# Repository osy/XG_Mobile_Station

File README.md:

XG Mobile Dock
==============
This open source hardware allows you to connect any PCIe card to an ASUS ROG device with the XG Mobile connector.

The standard variant is a drop-in replacement PCB for the [XG Station Pro Thunderbolt 3 eGPU dock][1]. It contains a built in USB 3.1 Gen 2 hub and a USB PD charger.

The lite variant is a standalone board that is compatible in dimensions with the [ADT-UT3G][6]. It requires a standard ATX power supply and passes through the USB to an external port.

## Features
* Up to PCIe 4.0 x8 support for 2021/2022/2023 ROG Flow
* Up to PCIe 4.0 x4 support for 2023 ROG Ally
* MCU handling cable detection and LEDs
* 65W USB PD charger (standard variant)
* 2 USB-C ports connected to a USB 3.1 Gen 2 hub (standard variant)
* 300W DC-DC power supply (standard variant)

## Getting Started
1. [Build the PCB](Docs/Build_Guide.md)
2. [Flash the board](#flashing-firmware)
3. [Install the software](#install-xgmactivator)

### Flashing Firmware
Lite boards only need to flash STM32 while the standard board requires writing two SPI flash as well.

#### STM32 MCU
1. Download `XG_Mobile_Dock_MCU.bin` from the latest release or [build your own](Docs/Build_Guide.md#mcu).
2. Download and install [ST32CubeProgrammer][2].
3. Connect your ST-LINK v2 to your computer. Note if you are using a cheap clone from Amazon or Aliexpress, the pin numbers printed on the device may be incorrect.
4. Connect the SWDIO, SWCLK, and GND pins to J10 on the board to the ST-LINK v2. Do not connect +3V3. If you are using an official ST-LINK, you will need a jumper wire from VAPP (pin 1) to VDD (pin 19).
5. Ensure the board is powered on so it can be programmed.
6. Open ST32CubeProgrammer and go to the "Erasing & programming" page (second icon on the left sidebar).
7. Browse and select the firmware file.
8. Check "Run after programming"
9. Click "Connect" on the right sidebar and then "Start Programming" on the left.

#### SPI Flash for TI USB PD
We will be using a Raspberry Pi, although most other SBC can also work as well as dedicated SPI flashers.

1. [Enable the SPI interface on the Raspberry Pi.][3]
2. Connect GND (Ground), SS (SPI0 CE0), CLK (SPI0 SCLK), MISO (SPI0 MISO), and MOSI (SPI0 MOSI) on J9 [to the Raspberry Pi][4].
3. Open a shell to the Raspberry Pi and install Flashrom: `sudo apt-get install flashrom`
4. Download `XG_Mobile_Dock_Charger.bin` from the latest release or [build your own](Docs/Build_Guide.md#ti-pd-controller).
5. Flash the firmware: `sudo flashrom -p linux_spi:dev=/dev/spidev0.0,spispeed=1000 -w XG_Mobile_Dock_Charger.bin`

#### SPI Flash for VIA USB Hub
We will be using a Raspberry Pi, although most other SBC can also work as well as dedicated SPI flashers.

1. [Enable the SPI interface on the Raspberry Pi.][3]
2. Connect GND (Ground), SS (SPI0 CE0), CLK (SPI0 SCLK), MISO (SPI0 MISO), and MOSI (SPI0 MOSI) on J13 [to the Raspberry Pi][4]. Note the order of the pins is different from J9.
3. Open a shell to the Raspberry Pi and install Flashrom if it is not already installed: `sudo apt-get install flashrom`
4. Download `VL822_Q7_9043_Phantom_20220616.bin` from the latest release.
5. Flash the firmware: `sudo flashrom -p linux_spi:dev=/dev/spidev0.0,spispeed=1000 -w VL822_Q7_9043_Phantom_20220616.bin`

### Install XGMDriver
XGMDriver tricks ARMORY CRATE software into identifying the custom dock as an official XG Mobile device. Once installed, it should work even if ARMORY CRATE software is updated. You can check out the [source code here](XGMDriver).

1. Download `XGMDriverSetup.exe` from the latest release.
2. Run the installer making sure to correctly select AMD or NVIDIA depending on the vendor of the GPU you are installing.
3. If you need to swap between AMD and NVIDIA, uninstall from Control Panel or by running the installer again. Then you can re-install and select the right option.

## Troubleshooting

### Error 43 or no video output on NVIDIA GPUs
This is a well known issue with NVIDIA eGPUs. Once the eGPU is installed along with the correct drivers, you will need to install [this script][5].

### PCIe is only getting 3.0 speeds after hot plugging
You need to restart your device. For some reason, hot plugging results in 3.0 speeds.

### Unable to get 4.0 speeds
If you observe any of the following:
* GPU-Z changes between 4.0 and lower versions *when under load*
* You observe a lot of stuttering or < 10 FPS in 1% lows
* Windows behaves extremely slowly (moving the mouse cursor will take > 1 sec to respond)
* Event viewer for System shows multiple times: "WHEA-Logger Event ID:17 - A corrected hardware error has occurred"

Then the device is having trouble sustaining PCIe 4.0 speeds. This can be caused by any combination of the following issues:

1. The board was not manufactured properly with impedance matching or the high speed connectors were not properly soldered. Verify that the boards were manufactured with the correct specifications and test multiple boards.
2. The GPU is malfunctioning or is not mounted correctly. Make sure you can obtain PCIe 4.0 speeds on a desktop PC.
3. The XGM cable is not connected to the board correctly. Make sure the two 40P connectors are tight and the metal bar is locked over the connector to prevent unintentional loosening. Make sure the shielding screw is tightly screwed to the screw terminal next to the connector. Make sure the cable isn't twisted or bent any more than it needs to be. If the XGM cable came coiled up, try to carefully straighten it.
4. The XGM cable is not manufactured correctly. The official XGM device only supports PCIe 3.0 speeds so the cable is only rated for PCIe 3.0. We found that some cables are easier to get 4.0 speeds working than other cables so there is some manufacturing variance.

You can run FurMark for a long duration and observe the GPU load to check that it is able to maintain 4.0 speeds. If the GPU is constantly trying to switch speeds, you will observe large FPS drops and large dips in the GPU usage percentage. You can also use CUDA-Z to check the access speeds while under load.

If you cannot maintain PCIe 4.0 speeds, you can always do a hot-unplug and hot-plug to force it to run in PCIe 3.0 mode.

### No popup when XGM is connected
Sometimes, the device will not be detected and you can flip the lock switch off and on again to force the software to re-detect the device.

### "It appears that your XG Mobile is not properly connected..."
If you get a pop-up saying XG Mobile is not properly connected, make sure [XGMDriver](#install-xgmdriver) is installed. If this is still an issue with XGMDriver installed, there is likely a connection issue with the cable.

### ASUS Driver install popup on reboot
Re-install XGMDriver to inhibit the ASUS driver popup.

### Lite: USB is not detected
The lite board does not have USB orientation detection. Try flipping the USB-C cable upside down and try again.

## References
Knowledge base for all things XGM gathered from reverse engineering the hardware and software.

* [XGM connector information](Docs/Connector.md)
* [XGM software interfaces](Docs/Software.md)
* [MCU command interface](Docs/MCU.md)
* [PCB design diary](Docs/Diary.md)
* [Reversed ACPI tables](Docs/ACPI_Annotated.asl)
* [Reversed BIOS detection](Docs/BIOS_Detect.c)

## Related Projects

* [Modified Lite design with redrivers for improved performance (not yet working)](https://github.com/Alecu100/XG_Mobile_Station/tree/flow_v2)

[1]: https://www.asus.com/motherboards-components/external-graphics-docks/all-series/xg-station-pro/
[2]: https://www.st.com/en/development-tools/stm32cubeprog.html
[3]: https://www.raspberrypi-spy.co.uk/2014/08/enabling-the-spi-interface-on-the-raspberry-pi/
[4]: https://pinout.xyz
[5]: https://egpu.io/nvidia-error43-fixer
[6]: https://www.adt.link/product/UT3G.html

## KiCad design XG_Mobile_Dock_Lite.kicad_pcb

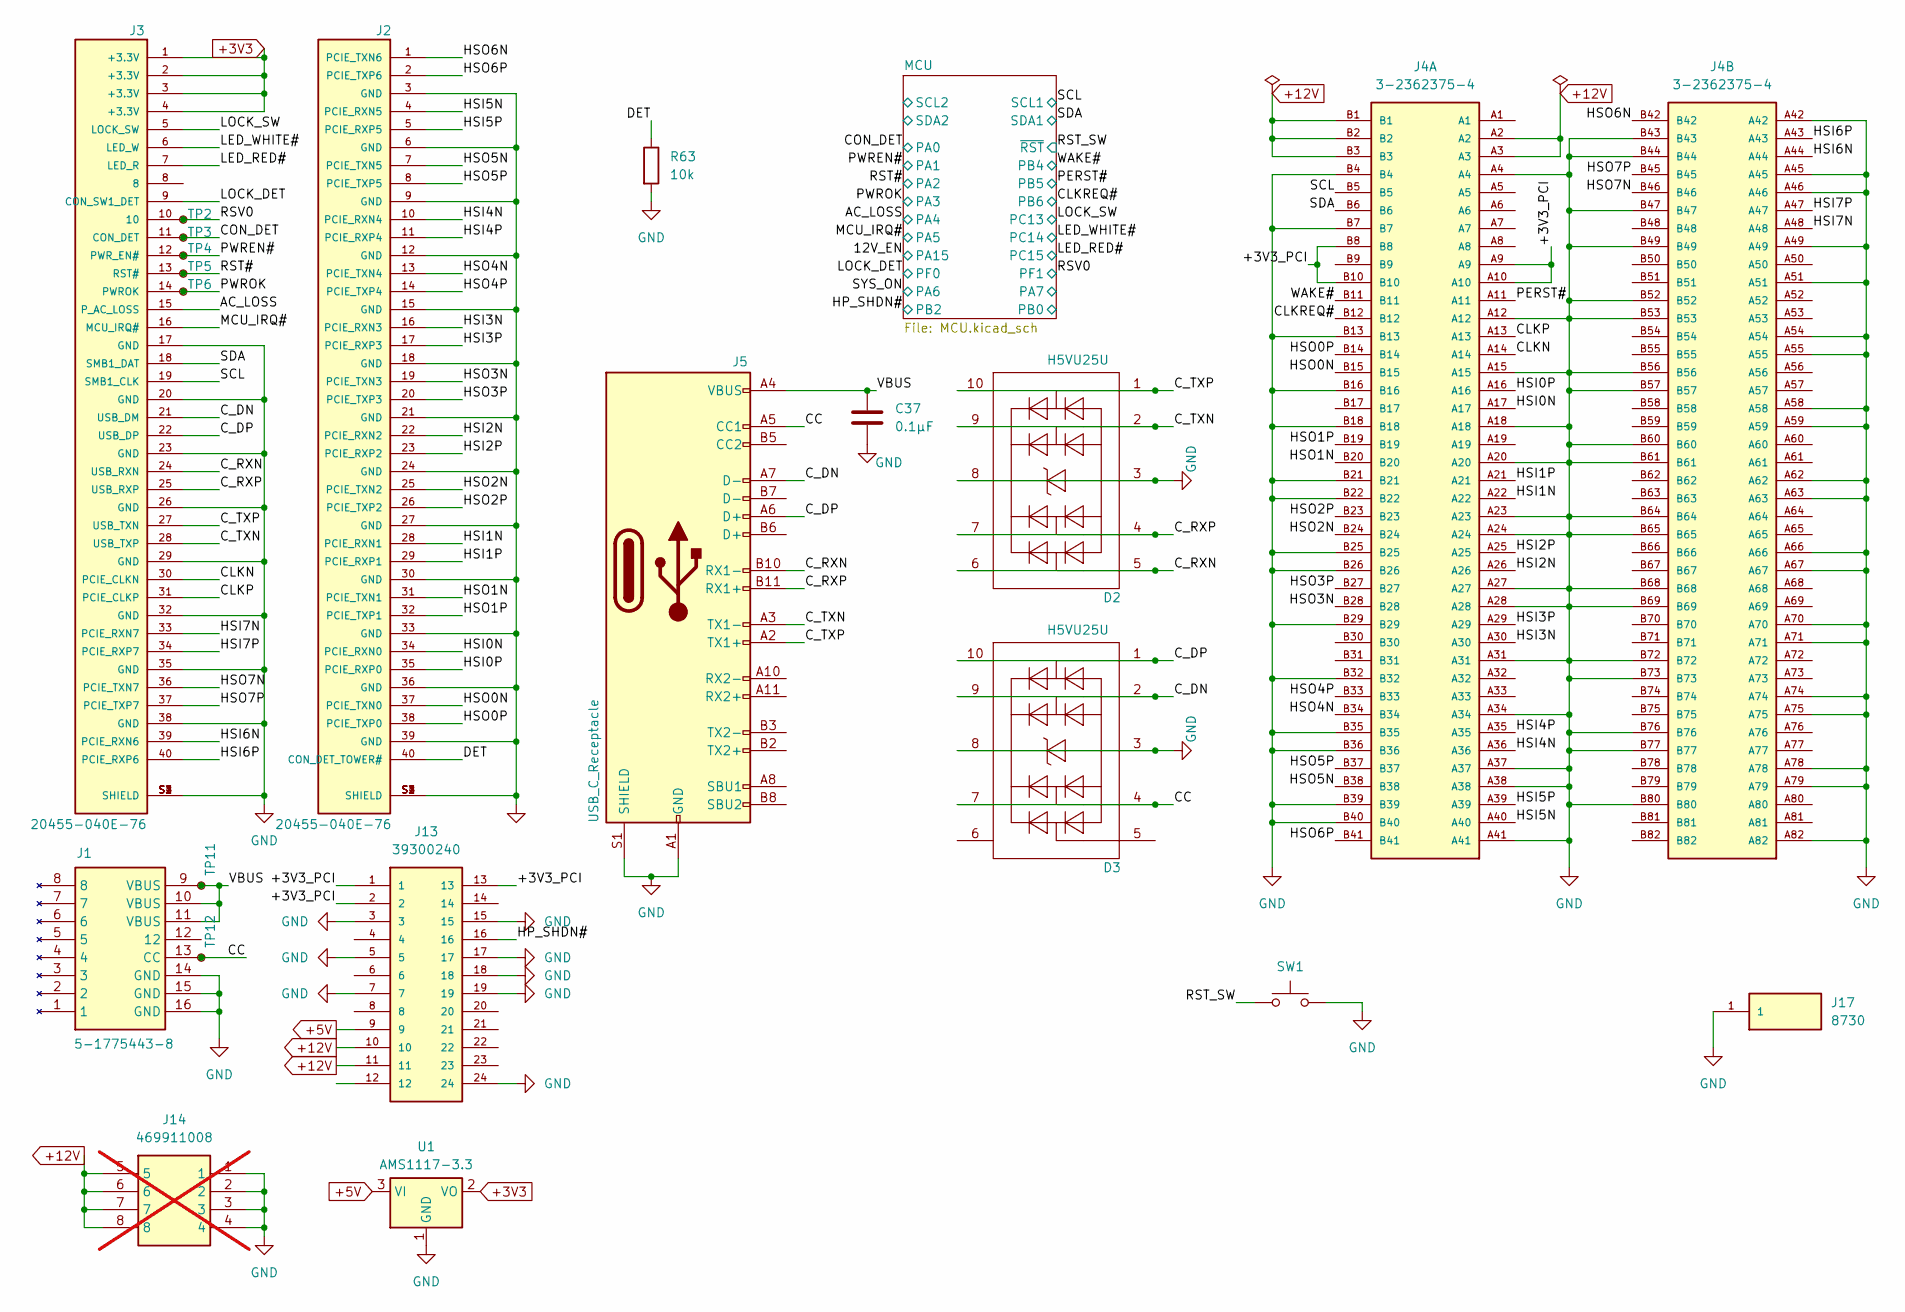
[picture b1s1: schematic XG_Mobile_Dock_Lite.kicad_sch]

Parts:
C37: 0.1μF; C_0402_1005Metric; Part_Number CL05B104KO5NNNC; LCSC C1525
D2, D3: H5VU25U; AZ1045-04F; Part_Number H5VU25U; LCSC C7420374
J1: 5-1775443-8; Manufacturer_Part_Number 5-1775443-8
J2, J3: 20455-040E-76; Part_Number 20455-040E-76; LCSC C5160883
J4: 3-2362375-4; CONN-SMD_164P-P1.00-V_3133; Part_Number 3113-113T; LCSC C404104
J5: USB_C_Receptacle; USB-C-SMD_TYPE-C-24P-QT; Part_Number TYPE-C 24P QT; LCSC C2681555
J13: 39300240; CON_39300240; Part_Number ZX-5557-4.2-2-12PWZ; LCSC C7541574
J14: 469911008; CON_469911008; Part_Number 469911008; LCSC C17470577; not fitted
J17: 8730; KEYSTONE_8730; PARTREV C
R63: 10k; R_0402_1005Metric; Part_Number 0402WGF1002TCE; LCSC C25744
SW1: SW_Push; SW_SPST_SKQG_WithStem; Part_Number TS-1187A-B-A-B; LCSC C318884
TP2, TP3, TP4, TP5, TP6, TP11, TP12: TestPoint_Small; TestPoint_Pad_D1.0mm
U1: AMS1117-3.3; SOT-223-3_TabPin2; Part_Number AMS1117-3.3; LCSC C6186

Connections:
+3V3: J3.1 (+3.3V), J3.2 (+3.3V), J3.3 (+3.3V), J3.4 (+3.3V), U1.2 (VO); also elsewhere on the board
+5V: J13.9, U1.3 (VI); also elsewhere on the board
+12V: J4.A2, J4.A3, J4.B1, J4.B2, J4.B3, J13.10, J13.11, J14.5, J14.6, J14.7, J14.8; also elsewhere on the board
/+3V3_PCI: J4.A9, J4.A10, J4.B8, J4.B10, J13.1, J13.2, J13.13
/AC_LOSS: J3.15 (P_AC_LOSS); also elsewhere on the board
/CC: D3.4 (I/O_3), D3.7 (NC), J1.13 (CC), J5.A5 (CC1), TP12.1
/CLKN: J3.30 (PCIE_CLKN), J4.A14
/CLKP: J3.31 (PCIE_CLKP), J4.A13
/CLKREQ#: J4.B12; also elsewhere on the board
/CON_DET: J3.11 (CON_DET), TP3.1; also elsewhere on the board
/C_DN: D3.2 (I/O_2), D3.9 (NC), J3.21 (USB_DM), J5.A7 (D-)
/C_DP: D3.1 (I/O_1), D3.10 (NC), J3.22 (USB_DP), J5.A6 (D+)
/C_RXN: D2.5 (I/O_4), D2.6 (NC), J3.24 (USB_RXN), J5.B10 (RX1-)
/C_RXP: D2.4 (I/O_3), D2.7 (NC), J3.25 (USB_RXP), J5.B11 (RX1+)
/C_TXN: D2.2 (I/O_2), D2.9 (NC), J3.28 (USB_TXP), J5.A3 (TX1-)
/C_TXP: D2.1 (I/O_1), D2.10 (NC), J3.27 (USB_TXN), J5.A2 (TX1+)
/DET: J2.40 (CON_DET_TOWER#), R63.1
/HP_SHDN#: J13.16; also elsewhere on the board
/HSI0N: J2.34 (PCIE_RXN0), J4.A17
/HSI0P: J2.35 (PCIE_RXP0), J4.A16
/HSI1N: J2.28 (PCIE_RXN1), J4.A22
/HSI1P: J2.29 (PCIE_RXP1), J4.A21
/HSI2N: J2.22 (PCIE_RXN2), J4.A26
/HSI2P: J2.23 (PCIE_RXP2), J4.A25
/HSI3N: J2.16 (PCIE_RXN3), J4.A30
/HSI3P: J2.17 (PCIE_RXP3), J4.A29
/HSI4N: J2.10 (PCIE_RXN4), J4.A36
/HSI4P: J2.11 (PCIE_RXP4), J4.A35
/HSI5N: J2.4 (PCIE_RXN5), J4.A40
/HSI5P: J2.5 (PCIE_RXP5), J4.A39
/HSI6N: J3.39 (PCIE_RXN6), J4.A44
/HSI6P: J3.40 (PCIE_RXP6), J4.A43
/HSI7N: J3.33 (PCIE_RXN7), J4.A48
/HSI7P: J3.34 (PCIE_RXP7), J4.A47
/HSO0N: J2.37 (PCIE_TXN0), J4.B15
/HSO0P: J2.38 (PCIE_TXP0), J4.B14
/HSO1N: J2.31 (PCIE_TXN1), J4.B20
/HSO1P: J2.32 (PCIE_TXP1), J4.B19
/HSO2N: J2.25 (PCIE_TXN2), J4.B24
/HSO2P: J2.26 (PCIE_TXP2), J4.B23
/HSO3N: J2.19 (PCIE_TXN3), J4.B28
/HSO3P: J2.20 (PCIE_TXP3), J4.B27
/HSO4N: J2.13 (PCIE_TXN4), J4.B34
/HSO4P: J2.14 (PCIE_TXP4), J4.B33
/HSO5N: J2.7 (PCIE_TXN5), J4.B38
/HSO5P: J2.8 (PCIE_TXP5), J4.B37
/HSO6N: J2.1 (PCIE_TXN6), J4.B42
/HSO6P: J2.2 (PCIE_TXP6), J4.B41
/HSO7N: J3.36 (PCIE_TXN7), J4.B46
/HSO7P: J3.37 (PCIE_TXP7), J4.B45
/LED_RED#: J3.7 (LED_R); also elsewhere on the board
/LED_WHITE#: J3.6 (LED_W); also elsewhere on the board
/LOCK_DET: J3.9 (CON_SW1_DET); also elsewhere on the board
/LOCK_SW: J3.5 (LOCK_SW); also elsewhere on the board
/MCU_IRQ#: J3.16 (MCU_IRQ#); also elsewhere on the board
/PERST#: J4.A11; also elsewhere on the board
/PWREN#: J3.12 (PWR_EN#), TP4.1; also elsewhere on the board
/PWROK: J3.14 (PWROK), TP6.1; also elsewhere on the board
/RST#: J3.13 (RST#), TP5.1; also elsewhere on the board
/RST_SW: SW1.1; also elsewhere on the board
/RSV0: J3.10, TP2.1; also elsewhere on the board
/SCL: J3.19 (SMB1_CLK), J4.B5; also elsewhere on the board
/SDA: J3.18 (SMB1_DAT), J4.B6; also elsewhere on the board
/VBUS: C37.1, J1.9 (VBUS), J1.10 (VBUS), J1.11 (VBUS), J5.A4 (VBUS), J5.A9 (VBUS), J5.B4 (VBUS), J5.B9 (VBUS), TP11.1
/WAKE#: J4.B11; also elsewhere on the board
GND: C37.2, D2.3 (GND), D2.8 (GND), D3.3 (GND), D3.8 (GND), J1.14 (GND), J1.15 (GND), J1.16 (GND), J2.3 (GND), J2.6 (GND), J2.9 (GND), J2.12 (GND), J2.15 (GND), J2.18 (GND), J2.21 (GND), J2.24 (GND), J2.27 (GND), J2.30 (GND), J2.33 (GND), J2.36 (GND), J2.39 (GND), J2.S1 (SHIELD), J2.S2 (SHIELD), J2.S3 (SHIELD), J2.S4 (SHIELD), J3.17 (GND), J3.20 (GND), J3.23 (GND), J3.26 (GND), J3.29 (GND), J3.32 (GND), J3.35 (GND), J3.38 (GND), J3.S1 (SHIELD), J3.S2 (SHIELD), J3.S3 (SHIELD), J3.S4 (SHIELD), J4.A4, J4.A12, J4.A15, J4.A18, J4.A20, J4.A23, J4.A24, J4.A27, J4.A28, J4.A31, J4.A34, J4.A37, J4.A38, J4.A41, J4.A42, J4.A45, J4.A46, J4.A49, J4.A51, J4.A54, J4.A55, J4.A58, J4.A59, J4.A62, J4.A63, J4.A66, J4.A67, J4.A70, J4.A71, J4.A74, J4.A75, J4.A78, J4.A79, J4.A82, J4.B4, J4.B7, J4.B13, J4.B16, J4.B18, J4.B21, J4.B22, J4.B25, J4.B26, J4.B29, J4.B32, J4.B35, J4.B36, J4.B39, J4.B40, J4.B43, J4.B44, J4.B47, J4.B49, J4.B52, J4.B53, J4.B56, J4.B57, J4.B60, J4.B61, J4.B64, J4.B65, J4.B68, J4.B69, J4.B72, J4.B73, J4.B76, J4.B77, J4.B80, J5.A1 (GND), J5.A12 (GND), J5.B1 (GND), J5.B12 (GND), J5.S1 (SHIELD), J13.3, J13.5, J13.7, J13.15, J13.17, J13.18, J13.19, J13.24, J14.1, J14.2, J14.3, J14.4, J17.1, R63.2, SW1.2, U1.1 (GND); also elsewhere on the board

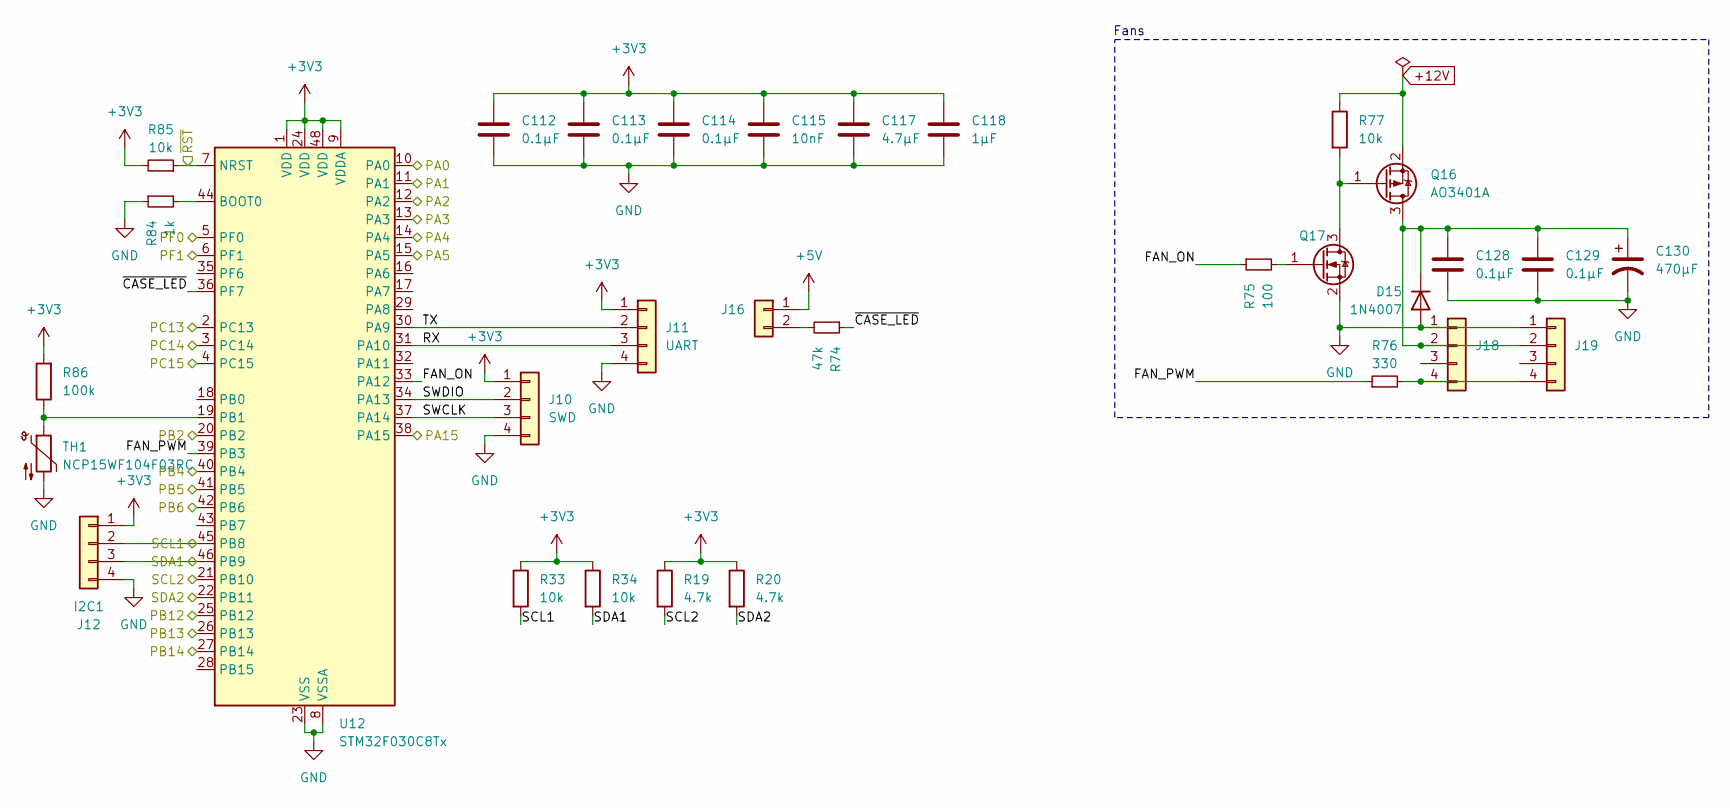
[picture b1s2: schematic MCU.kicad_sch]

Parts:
C112, C113, C114: 0.1µF; C_0402_1005Metric; Part_Number CL05B104KB54PNC; LCSC C307331
C115: 10nF; C_0402_1005Metric; Part_Number CL05B103KB5NNNC; LCSC C15195
C117: 4.7µF; C_0402_1005Metric; Part_Number CL05A475MP5NRNC; LCSC C23733
C118: 1µF; C_0402_1005Metric; Part_Number CL05A105KA5NQNC; LCSC C52923
C128, C129: 0.1µF; C_0603_1608Metric; Part_Number CC0603KRX7R9BB104; LCSC C14663
C130: 470µF; CP_Radial_D10.0mm_P5.00mm; Part_Number EGT477M1HG16RRS0P; LCSC C3015599
D15: 1N4007; D_SOD-123F; Part_Number 1N4007W; LCSC C18199088
J10: SWD; PinHeader_1x04_P2.54mm_Vertical; Part_Number 2.54-1*4; LCSC C5116483
J11: UART; PinHeader_1x04_P2.54mm_Vertical; Part_Number 2.54-1*4; LCSC C5116483
J12: I2C1; PinHeader_1x04_P2.54mm_Vertical; Part_Number 2.54-1*4; LCSC C5116483
J16: JST_PH_S2B-PH-K_1x02_P2.00mm_Horizontal; Part_Number S2B-PH-KL(LF)(SN); LCSC C160237
J18, J19: CONN_SD-47053-001_H10p00_MOL; Part_Number 470531000; LCSC C240840
Q16: AO3401A; SOT-23; Part_Number AO3401A; LCSC C15127
Q17: 2N7002W; SOT-323-3_L2.0-W1.3-P1.30-LS2.1-BR; Part_Number 2N7002W; LCSC C7420322
R19, R20: 4.7k; R_0402_1005Metric; Part_Number 0402WGF4701TCE; LCSC C25900
R33, R34, R77, R85: 10k; R_0402_1005Metric; Part_Number 0402WGF1002TCE; LCSC C25744
R74: 47k; R_0402_1005Metric; Part_Number 0402WGF4702TCE; LCSC C25792
R75: 100; R_0402_1005Metric; Part_Number 0402WGF1000TCE; LCSC C25076
R76: 330; R_0402_1005Metric; Part_Number 0402WGF3300TCE; LCSC C25104
R84: 1k; R_0402_1005Metric; Part_Number 0402WGF1001TCE; LCSC C11702
R86: 100k; R_0402_1005Metric; Part_Number 0402WGF1003TCE; LCSC C25741
TH1: NCP15WF104F03RC; R_0402_1005Metric; Part_Number NCP15WF104F03RC; LCSC C77130
U12: STM32F030C8Tx; LQFP-48_7x7mm_P0.5mm; Part_Number STM32F030C8T6; LCSC C23922

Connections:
+3V3: C112.1, C113.1, C114.1, C115.1, C117.1, C118.1, J10.1, J11.1, J12.1, R19.1, R20.1, R33.1, R34.1, R85.2, R86.2, U12.1 (VDD), U12.9 (VDDA), U12.24 (VDD), U12.48 (VDD); also elsewhere on the board
+5V: J16.1; also elsewhere on the board
+12V: Q16.2 (S), R77.1; also elsewhere on the board
/12V_EN: U12.38 (PA15)
/AC_LOSS: U12.14 (PA4); also elsewhere on the board
/CLKREQ#: U12.42 (PB6); also elsewhere on the board
/CON_DET: U12.10 (PA0); also elsewhere on the board
/HP_SHDN#: U12.20 (PB2); also elsewhere on the board
/LED_RED#: U12.4 (PC15); also elsewhere on the board
/LED_WHITE#: U12.3 (PC14); also elsewhere on the board
/LOCK_DET: U12.5 (PF0); also elsewhere on the board
/LOCK_SW: U12.2 (PC13); also elsewhere on the board
/MCU/FAN_ON: R75.1, U12.33 (PA12)
/MCU/FAN_PWM: R76.1, U12.39 (PB3)
/MCU/PB12: U12.25 (PB12)
/MCU/PB13: U12.26 (PB13)
/MCU/PB14: U12.27 (PB14)
/MCU/RX: J11.3, U12.31 (PA10)
/MCU/SCL2: R19.2, U12.21 (PB10)
/MCU/SDA2: R20.2, U12.22 (PB11)
/MCU/SWCLK: J10.3, U12.37 (PA14)
/MCU/SWDIO: J10.2, U12.34 (PA13)
/MCU/TX: J11.2, U12.30 (PA9)
/MCU/~CASE_LED: R74.1, U12.36 (PF7)
/MCU_IRQ#: U12.15 (PA5); also elsewhere on the board
/PERST#: U12.41 (PB5); also elsewhere on the board
/PWREN#: U12.11 (PA1); also elsewhere on the board
/PWROK: U12.13 (PA3); also elsewhere on the board
/RST#: U12.12 (PA2); also elsewhere on the board
/RST_SW: R85.1, U12.7 (NRST); also elsewhere on the board
/RSV0: U12.6 (PF1); also elsewhere on the board
/SCL: J12.2, R33.2, U12.45 (PB8); also elsewhere on the board
/SDA: J12.3, R34.2, U12.46 (PB9); also elsewhere on the board
/WAKE#: U12.40 (PB4); also elsewhere on the board
GND: C112.2, C113.2, C114.2, C115.2, C117.2, C118.2, C128.2, C129.2, C130.2, D15.2 (A), J10.4, J11.4, J12.4, J18.1, J19.1, Q17.2 (S), R84.1, TH1.2, U12.8 (VSSA), U12.23 (VSS), U12.47 (VSS); also elsewhere on the board
unnamed: C128.1, C129.1, C130.1, D15.1 (K), J18.2, J19.2, Q16.3 (D)
unnamed: J16.2, R74.2
unnamed: J18.4, J19.4, R76.2
unnamed: Q16.1 (G), Q17.3 (D), R77.2
unnamed: Q17.1 (G), R75.2
unnamed: R84.2, U12.44 (BOOT0)
unnamed: R86.1, TH1.1, U12.19 (PB1)

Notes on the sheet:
Fans

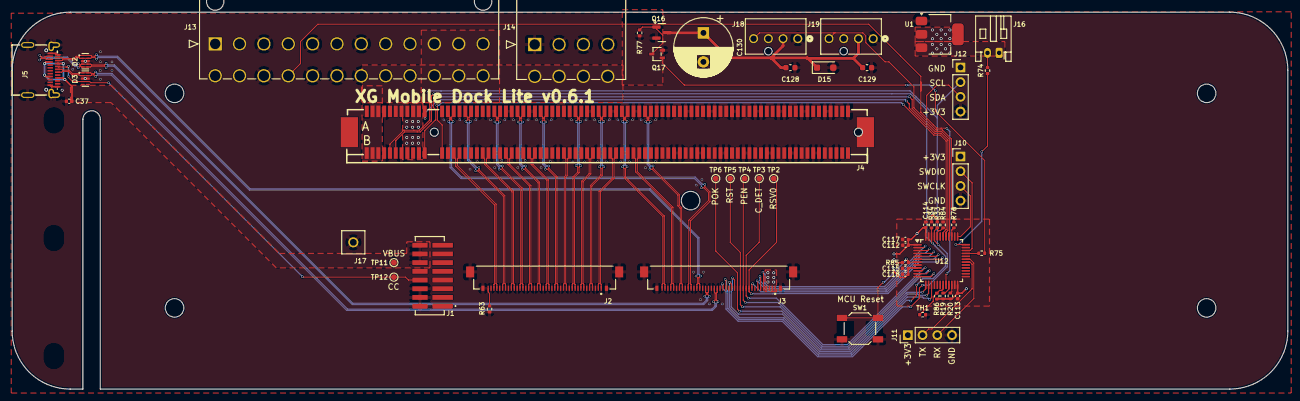
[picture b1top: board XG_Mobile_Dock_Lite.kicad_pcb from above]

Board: 4 copper layers, 220.0 x 65.0 mm, 52 parts (0 on the bottom side), 82 nets.

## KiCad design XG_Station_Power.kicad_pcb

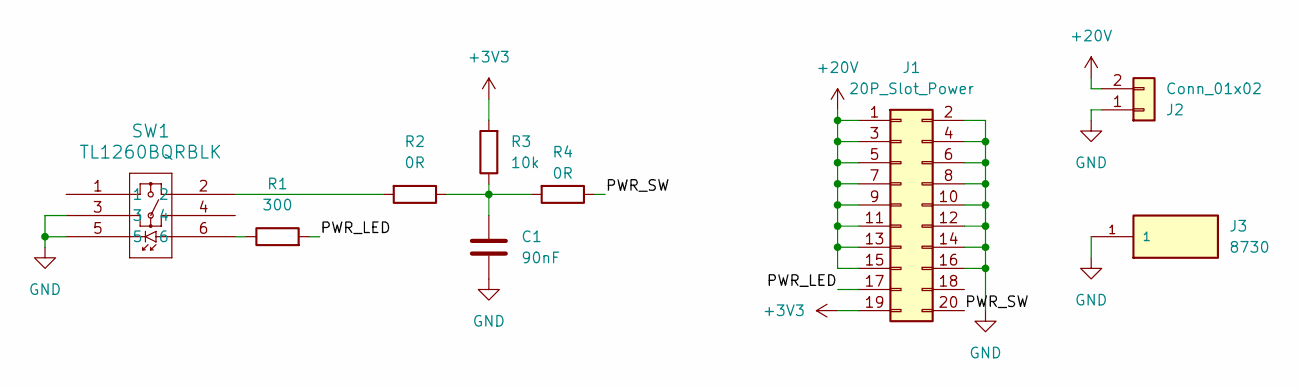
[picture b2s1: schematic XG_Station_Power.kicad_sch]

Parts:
C1: 90nF; C_0402_1005Metric
J1: 20P_Slot_Power
J2: Conn_01x02; 2351970-1
J3: 8730; KEYSTONE_8730; PARTREV C
R1: 300; R_0603_1608Metric
R2, R4: 0R; R_0402_1005Metric
R3: 10k; R_0402_1005Metric
SW1: TL1260BQRBLK; TL1260_EWI

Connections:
+3V3: J1.19, R3.2
+20V: J1.1, J1.3, J1.5, J1.7, J1.9, J1.11, J1.13, J1.15, J2.2
/PWR_LED: J1.17, R1.2
/PWR_SW: J1.20, R4.1
GND: C1.2, J1.2, J1.4, J1.6, J1.8, J1.10, J1.12, J1.14, J1.16, J2.1, J3.1, SW1.3, SW1.5
unnamed: C1.1, R2.1, R3.1, R4.2
unnamed: R1.1, SW1.6
unnamed: R2.2, SW1.2

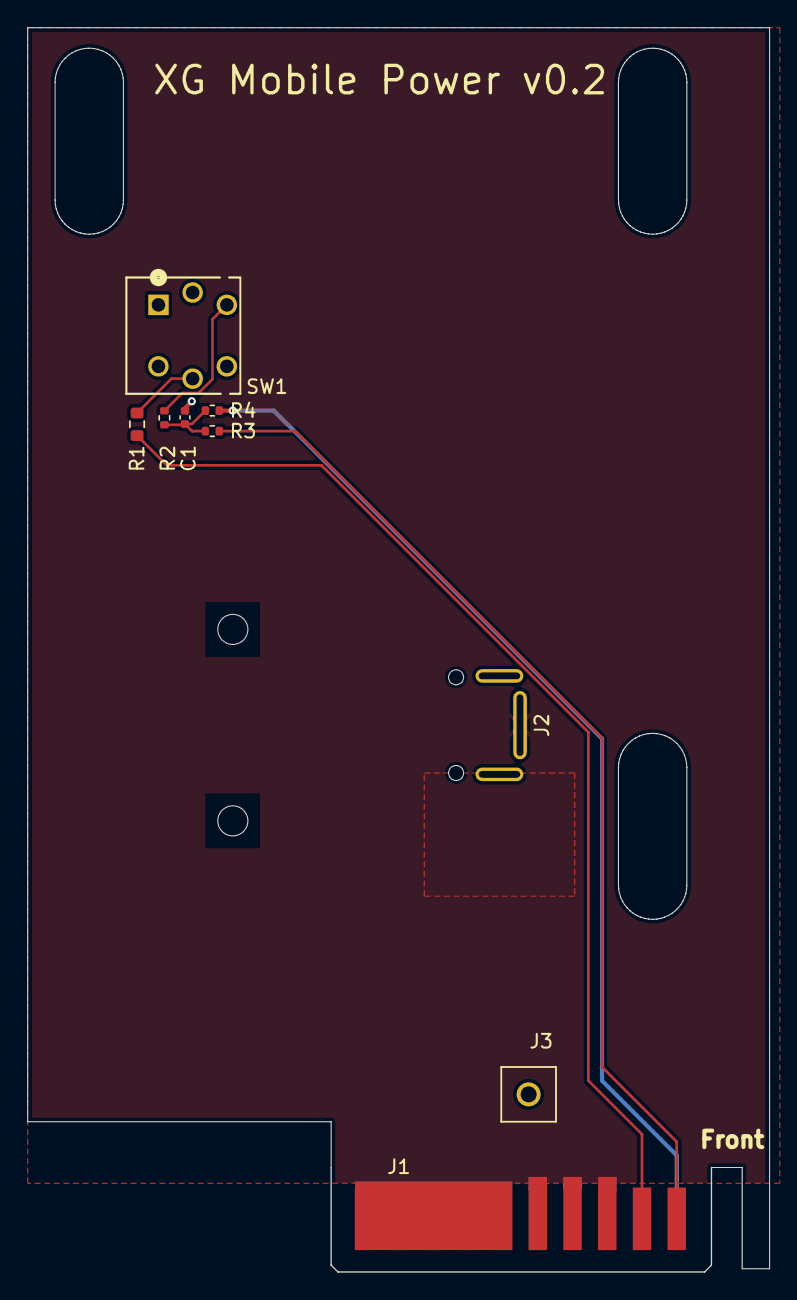
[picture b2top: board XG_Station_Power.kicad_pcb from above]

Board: 2 copper layers, 54.2 x 91.0 mm, 11 parts (0 on the bottom side), 8 nets.

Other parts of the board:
Hole: MountingHole_2.2mm_M2
Hole#2: MountingHole_2.2mm_M2

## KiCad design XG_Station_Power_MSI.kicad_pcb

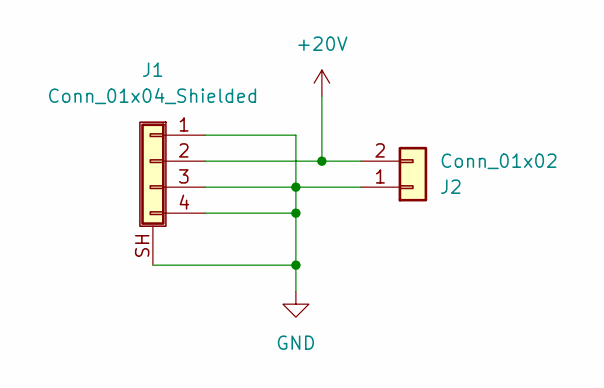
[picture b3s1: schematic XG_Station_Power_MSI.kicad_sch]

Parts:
J1: Conn_01x04_Shielded; MSI_Charger
J2: Conn_01x02; 2P_Slot_Power

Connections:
+20V: J1.2, J2.2
GND: J1.1, J1.3, J1.4, J1.SH (Shield), J2.1

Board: 2 copper layers, 4 parts (0 on the bottom side), 2 nets, no tracks yet.

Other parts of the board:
Hole: MountingHole_2.2mm_M2
Hole#2: MountingHole_2.2mm_M2

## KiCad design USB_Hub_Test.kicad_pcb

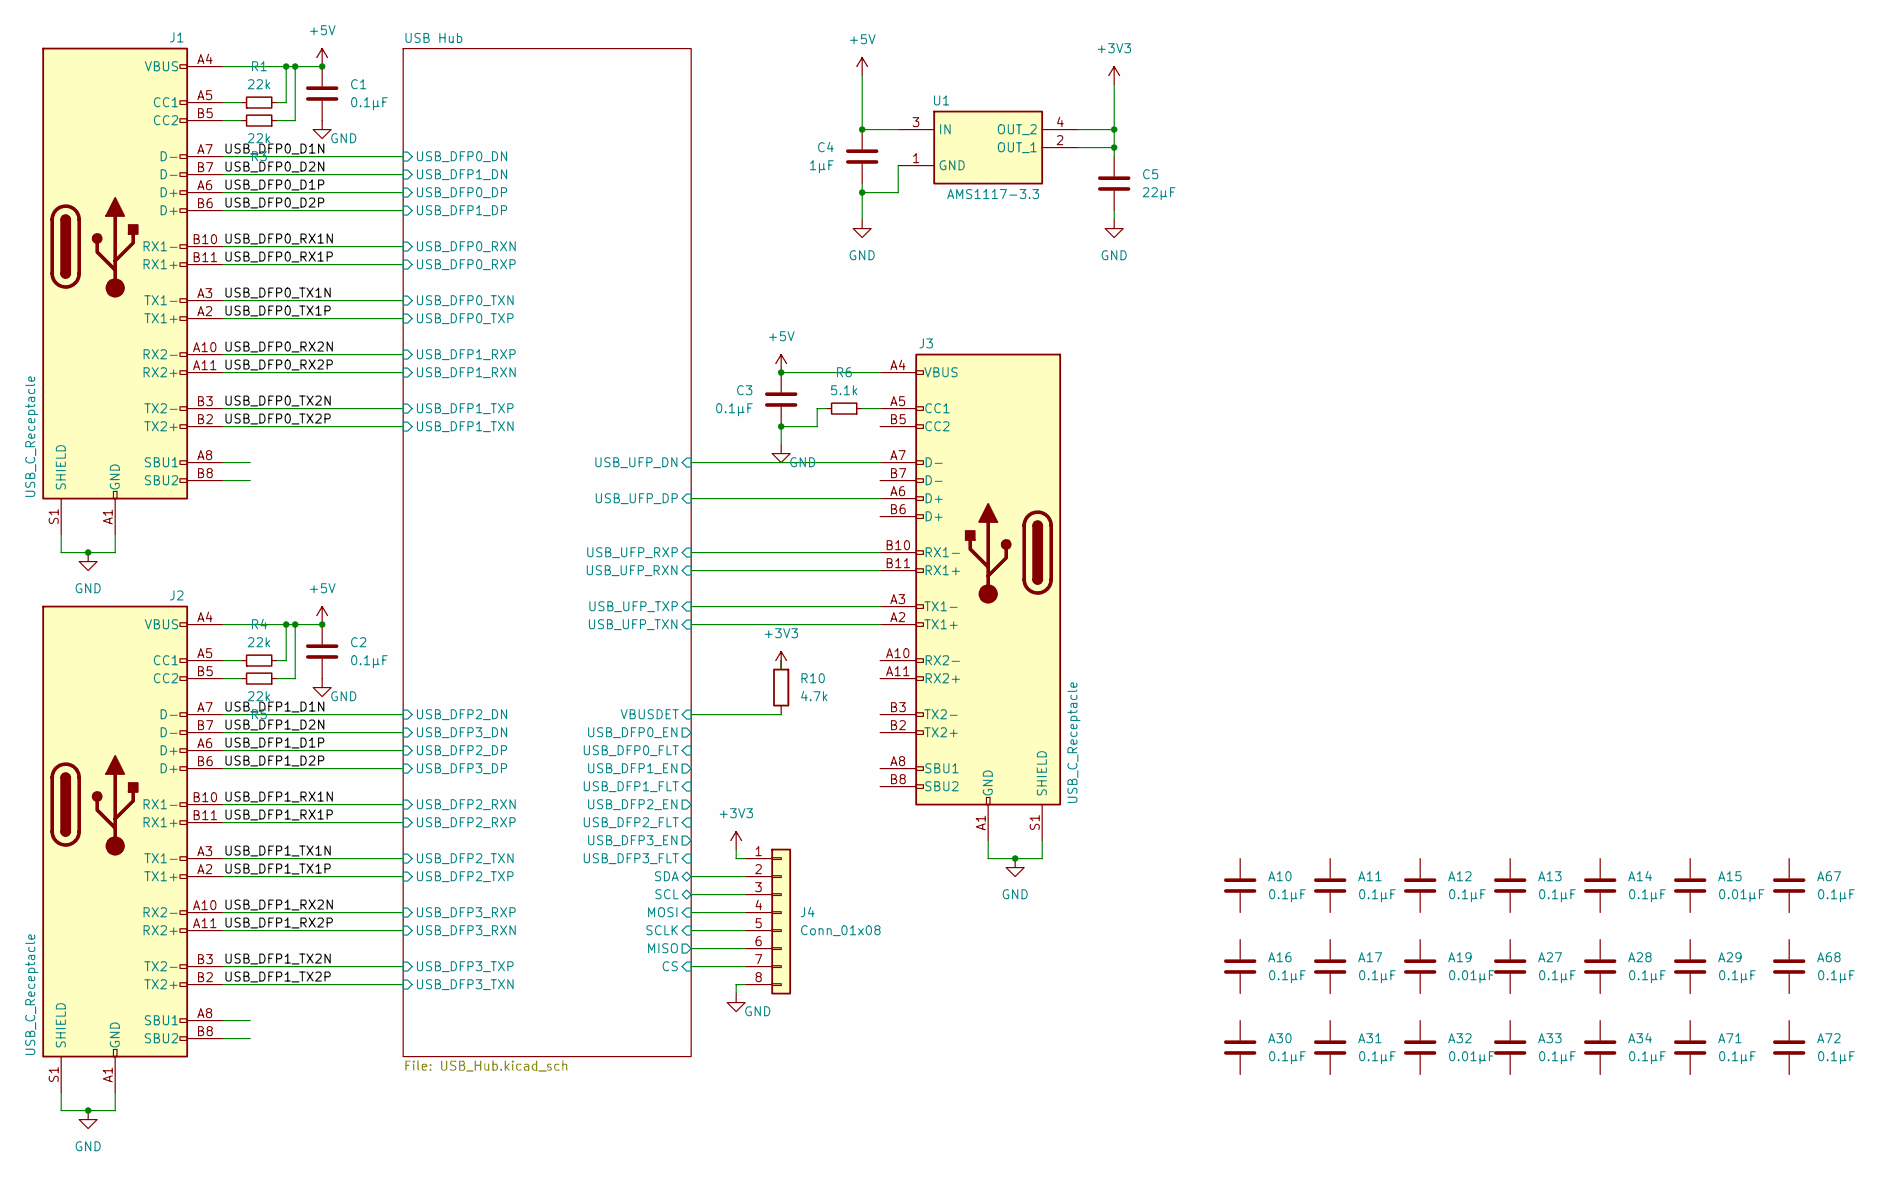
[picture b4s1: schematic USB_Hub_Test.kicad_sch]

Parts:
A10, A11, A12, A13, A14, A16, A17, A27, A28, A29, A30, A31, A33, A34, A67, A68, A71, A72: 0.1µF; C_0402_1005Metric; Part_Number CL05B104KB54PNC; LCSC C307331
A15, A19, A32: 0.01µF; C_0402_1005Metric; Part_Number CL05B103KB5NNNC; LCSC C15195
C1, C2, C3: 0.1μF; C_0402_1005Metric; Part_Number CL05B104KO5NNNC; LCSC C1525
C4: 1µF; C_0603_1608Metric; Part_Number CL10A105KB8NNNC; LCSC C15849
C5: 22μF; C_0603_1608Metric; Part_Number CL10A226MQ8NRNC; LCSC C59461
J1, J2, J3: USB_C_Receptacle; USB-C-SMD_TYPE-C-24P-QT; Part_Number TYPE-C 24P QT; LCSC C2681555
J4: Conn_01x08; PinHeader_1x08_P2.54mm_Vertical; Part_Number 2.54-1*8; LCSC C5156616
R1, R3, R4, R5: 22k; R_0402_1005Metric; Part_Number 0402WGF2202TCE; LCSC C25768
R6: 5.1k; R_0402_1005Metric; Part_Number 0402WGF5101TCE; LCSC C25905
R10: 4.7k; R_0402_1005Metric; Part_Number 0402WGF4701TCE; LCSC C25900
U1: AMS1117-3.3; SOT230P700X180-4N; Part_Number AMS1117-3.3; LCSC C6186

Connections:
+3V3: C5.1, J4.1, R10.2, U1.2 (OUT_1), U1.4 (OUT_2); also elsewhere on the board
+5V: C1.1, C2.1, C3.1, C4.1, J1.A4 (VBUS), J1.A9 (VBUS), J1.B4 (VBUS), J1.B9 (VBUS), J2.A4 (VBUS), J2.A9 (VBUS), J2.B4 (VBUS), J2.B9 (VBUS), J3.A4 (VBUS), J3.A9 (VBUS), J3.B4 (VBUS), J3.B9 (VBUS), R1.2, R3.1, R4.2, R5.1, U1.3 (IN)
/USB Hub/CS: J4.7; also elsewhere on the board
/USB Hub/MISO: J4.6; also elsewhere on the board
/USB Hub/MOSI: J4.4; also elsewhere on the board
/USB Hub/SCL: J4.3; also elsewhere on the board
/USB Hub/SCLK: J4.5; also elsewhere on the board
/USB Hub/SDA: J4.2; also elsewhere on the board
/USB Hub/USB_UFP_DN: J3.A7 (D-); also elsewhere on the board
/USB Hub/USB_UFP_DP: J3.A6 (D+); also elsewhere on the board
/USB Hub/USB_UFP_RXN: J3.B11 (RX1+); also elsewhere on the board
/USB Hub/USB_UFP_RXP: J3.B10 (RX1-); also elsewhere on the board
/USB Hub/USB_UFP_TXN: J3.A2 (TX1+); also elsewhere on the board
/USB Hub/USB_UFP_TXP: J3.A3 (TX1-); also elsewhere on the board
/USB Hub/VBUSDET: R10.1; also elsewhere on the board
/USB_DFP0_D1N: J1.A7 (D-); also elsewhere on the board
/USB_DFP0_D1P: J1.A6 (D+); also elsewhere on the board
/USB_DFP0_D2N: J1.B7 (D-); also elsewhere on the board
/USB_DFP0_D2P: J1.B6 (D+); also elsewhere on the board
/USB_DFP0_RX1N: J1.B10 (RX1-); also elsewhere on the board
/USB_DFP0_RX1P: J1.B11 (RX1+); also elsewhere on the board
/USB_DFP0_RX2N: J1.A10 (RX2-); also elsewhere on the board
/USB_DFP0_RX2P: J1.A11 (RX2+); also elsewhere on the board
/USB_DFP0_TX1N: J1.A3 (TX1-); also elsewhere on the board
/USB_DFP0_TX1P: J1.A2 (TX1+); also elsewhere on the board
/USB_DFP0_TX2N: J1.B3 (TX2-); also elsewhere on the board
/USB_DFP0_TX2P: J1.B2 (TX2+); also elsewhere on the board
/USB_DFP1_D1N: J2.A7 (D-); also elsewhere on the board
/USB_DFP1_D1P: J2.A6 (D+); also elsewhere on the board
/USB_DFP1_D2N: J2.B7 (D-); also elsewhere on the board
/USB_DFP1_D2P: J2.B6 (D+); also elsewhere on the board
/USB_DFP1_RX1N: J2.B10 (RX1-); also elsewhere on the board
/USB_DFP1_RX1P: J2.B11 (RX1+); also elsewhere on the board
/USB_DFP1_RX2N: J2.A10 (RX2-); also elsewhere on the board
/USB_DFP1_RX2P: J2.A11 (RX2+); also elsewhere on the board
/USB_DFP1_TX1N: J2.A3 (TX1-); also elsewhere on the board
/USB_DFP1_TX1P: J2.A2 (TX1+); also elsewhere on the board
/USB_DFP1_TX2N: J2.B3 (TX2-); also elsewhere on the board
/USB_DFP1_TX2P: J2.B2 (TX2+); also elsewhere on the board
GND: C1.2, C2.2, C3.2, C4.2, C5.2, J1.A1 (GND), J1.A12 (GND), J1.B1 (GND), J1.B12 (GND), J1.S1 (SHIELD), J2.A1 (GND), J2.A12 (GND), J2.B1 (GND), J2.B12 (GND), J2.S1 (SHIELD), J3.A1 (GND), J3.A12 (GND), J3.B1 (GND), J3.B12 (GND), J3.S1 (SHIELD), J4.8, R6.2, U1.1 (GND); also elsewhere on the board
unnamed: J1.A5 (CC1), R1.1
unnamed: J1.B5 (CC2), R3.2
unnamed: J2.A5 (CC1), R4.1
unnamed: J2.B5 (CC2), R5.2
unnamed: J3.A5 (CC1), R6.1
